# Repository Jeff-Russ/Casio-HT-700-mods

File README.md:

# Casio HT-700 Mods

This is a collection of instruction and schematics (in KiCAD with PCB designs) for modifying the 
Casio HT-700. More info will be available future commits.

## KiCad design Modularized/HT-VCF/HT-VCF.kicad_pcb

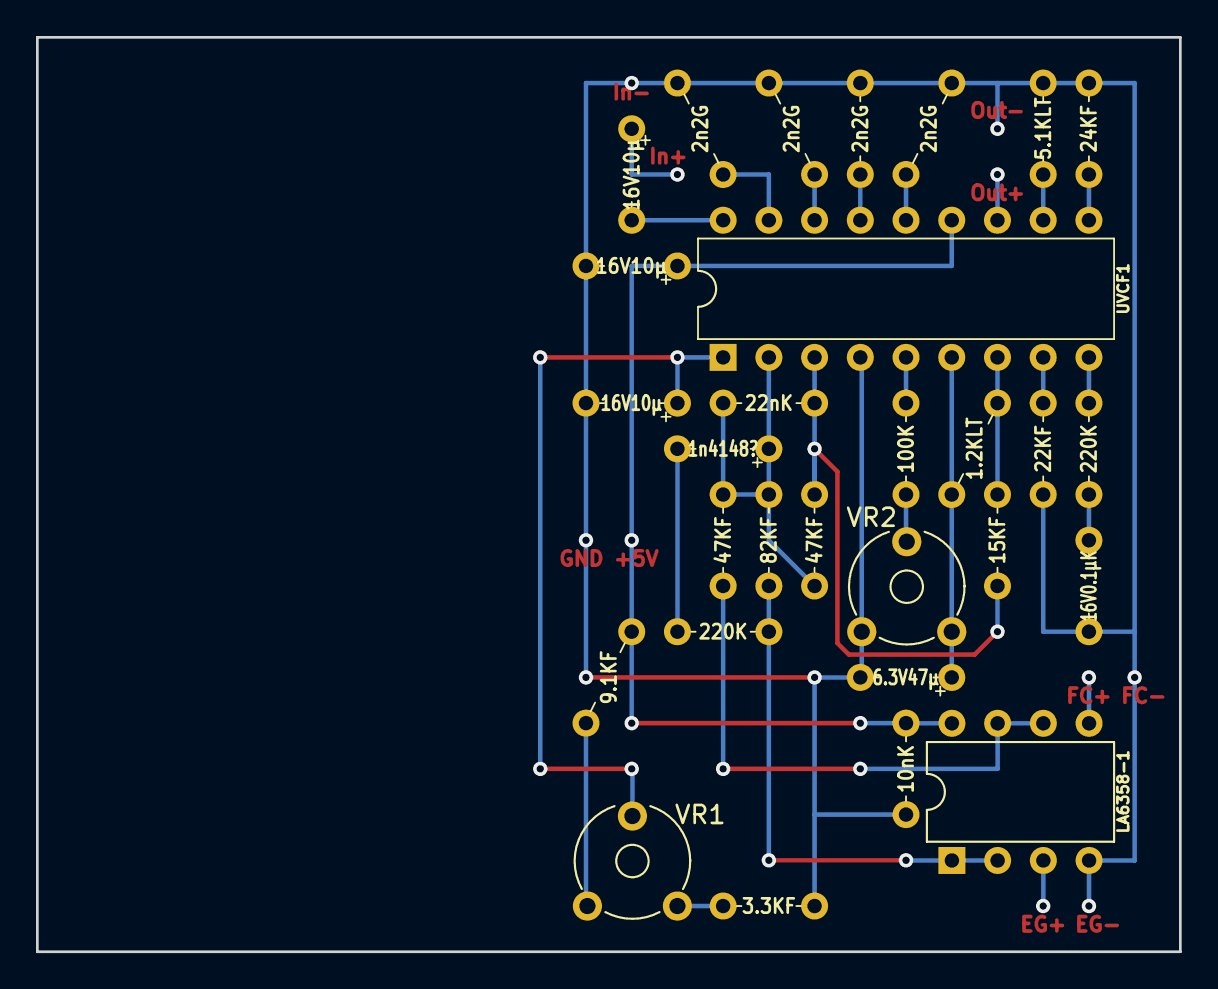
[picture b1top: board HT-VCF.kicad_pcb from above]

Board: 2 copper layers, 63.5 x 50.8 mm, 29 parts (0 on the bottom side), 24 nets.

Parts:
C1, C2, C7: 16V10µ; 200Mil_2TH_Polar_Generic
C3, C4: 2n2G; 200Mil_2TH_Up1_Generic
C5: 2n2G; 200Mil_2TH_Generic
C6: 2n2G; 200Mil_2TH_Dn1_Generic
C8: 22nK; 200Mil_2TH_Generic
C9: 16V0.1µK; 200Mil_2TH_Generic
C10: 6.3V47µ; 200Mil_2TH_Polar_Generic
C11: 10nK; 200Mil_2TH_Generic
D1: 1n4148?; 200Mil_2TH_Polar_Generic
LA6358-1: NJM4558; 300Mil_DIP8
R1: 5.1KLT; 200Mil_2TH_Generic
R2: 24KF; 200Mil_2TH_Generic
R3: 9.1KF; 200Mil_2TH_Dn1_Generic
R4: 3.3KF; 200Mil_2TH_Generic
R5, R12: 47KF; 200Mil_2TH_Generic
R6: 1.2KLT; 200Mil_2TH_Dn1_Generic
R7: 100K; 200Mil_2TH_Generic
R8: 22KF; 200Mil_2TH_Generic
R9, R10: 220K; 200Mil_2TH_Generic
R11: 82KF; 200Mil_2TH_Generic
R13: 15KF; 200Mil_2TH_Generic
UVCF1: NJM2090; 300Mil_DIP18
VR1: B500Ω; Potentiometer_Trimmer_Piher_PT-6v_Horizontal
VR2: B50K; Potentiometer_Trimmer_Piher_PT-6v_Horizontal

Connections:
+5VA: C1.1, C11.2, LA6358-1.8, R3.1, UVCF1.13
/RESO: C9.2, R9.2
/VBB: C7.1, UVCF1.1, VR1.2
GNDA: C1.2, C3.2, C4.2, C5.2, C6.2, C7.2, C9.1, C10.2, C11.1, LA6358-1.4, R1.1, R2.1, R4.2, R8.2, UVCF1.4, VR2.3
unnamed: C2.2, UVCF1.18
unnamed: C3.1, UVCF1.17
unnamed: C4.1, UVCF1.16
unnamed: C5.1, UVCF1.15
unnamed: C6.1, UVCF1.14
unnamed: C8.1, R5.2, R13.2, UVCF1.3
unnamed: C8.2, D1.1, R5.1, R11.2, R12.2, UVCF1.2
unnamed: C10.1, R6.1, UVCF1.6, VR2.1
unnamed: D1.2, R10.2
unnamed: LA6358-1.1, LA6358-1.2, R10.1, R11.1
unnamed: LA6358-1.6, LA6358-1.7, R12.1
unnamed: R1.2, UVCF1.11
unnamed: R2.2, UVCF1.10
unnamed: R3.2, VR1.3
unnamed: R4.1, VR1.1
unnamed: R7.1, UVCF1.5
unnamed: R7.2, VR2.2
unnamed: R8.1, UVCF1.8
unnamed: R9.1, UVCF1.9
unnamed: R6.2, R13.1, UVCF1.7

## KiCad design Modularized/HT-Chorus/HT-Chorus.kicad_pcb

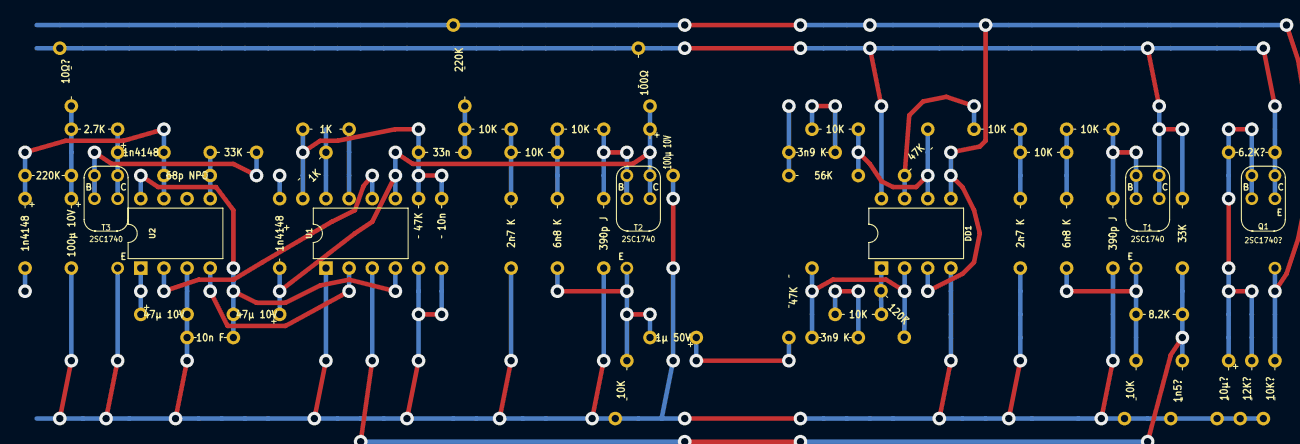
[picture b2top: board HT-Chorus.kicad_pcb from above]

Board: 4 copper layers, 61 parts (0 on the bottom side), 35 nets.

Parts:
C1, C13: 3n9 K; 200Mil_2TH_Generic
C2, C8: 2n7 K; 200Mil_2TH_Generic
C3, C9: 6n8 K; 200Mil_2TH_Generic
C4, C10: 390p J; 200Mil_2TH_Generic
C5: 1n5?; 200Mil_2TH_Generic
C6: 10n; 200Mil_2TH_Generic
C7: 33n; 200Mil_2TH_Generic
C11, C14: 100µ 10V; 200Mil_2TH_Polar_Generic
C12: 1µ 50V; 200Mil_2TH_Polar_Generic
C15, C17: 47µ 10V; 200Mil_2TH_Polar_Generic
C16: 10n F; 200Mil_2TH_Generic
C18: 68p NPO; 200Mil_2TH_Generic
C19: 10µ?; 200Mil_2TH_Polar_Generic
D1, D2, D3: 1n4148; 200Mil_2TH_Polar_Generic
DD1: NJM4558; 300Mil_DIP8
INPUT: REF**; Labled-Circle
LFO: REF**; Labled-Circle
OUTPUT: REF**; Labled-Circle
Q1: 2SC1740?; Universal_BJT_ECB_SM
R1: 56K; 200Mil_2TH_Generic
R2, R4, R5, R6, R7, R12, R13, R14, R16, R19: 10K; 200Mil_2TH_Generic
R3, R10, R17: 47K; 200Mil_2TH_Generic
R8, R23: 33K; 200Mil_2TH_Generic
R9: 8.2K; 200Mil_2TH_Generic
R11, R21: 220K; 200Mil_2TH_Generic
R15: 100Ω; 200Mil_2TH_Generic
R18: 120K; 200Mil_2TH_Generic
R20: 10Ω?; 200Mil_2TH_Generic
R22: 2.7K; 200Mil_2TH_Generic
R24, R25: 1K; 200Mil_2TH_Generic
R26: 6.2K?; 200Mil_2TH_Generic
R27: 12K?; 200Mil_2TH_Generic
R28: 10K?; 200Mil_2TH_Generic
T1, T2, T3: 2SC1740; Universal_BJT_ECB_SM
U1: MN3207; 300Mil_DIP8
U2: MN3102; 300Mil_DIP8
VE: REF**; Labled-Circle

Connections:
+5VA: DD1.8, Q1.2, R8.1, R15.1, R20.2, R26.1, T1.2
/Input: C1.2, R1.1
/Output: DD1.1, R18.2, R19.2
GNDA: C2.1, C4.1, C5.1, C6.2, C8.1, C10.1, C11.2, C14.2, C16.1, C17.2, C19.2, DD1.4, R7.1, R10.1, R16.1, R27.2, R28.2, T3.1, U1.1, U2.3
unnamed: C1.1, R2.1
unnamed: C2.2, R4.2, R5.1
unnamed: C3.1, R7.2, R9.1, T1.1
unnamed: C3.2, R5.2, R6.1
unnamed: C4.2, R6.2, T1.3
unnamed: C5.2, R8.2, R9.2, U1.3
unnamed: C6.1, C7.2, R10.2, R24.1, R25.1
unnamed: C7.1, R11.1, R12.1
unnamed: C8.2, R12.2, R13.1
unnamed: C9.2, R13.2, R14.1
unnamed: C10.2, R14.2, T2.3
unnamed: C11.1, C15.1, D1.2, R15.2, T2.2, U1.5
unnamed: C12.1, R17.1
unnamed: C9.1, C12.2, R16.2, T2.1
unnamed: C13.1, R19.1
unnamed: C13.2, DD1.2, R17.2, R18.1
unnamed: C14.1, R20.1, R21.1, R22.1
unnamed: C15.2, C16.2, U1.4, U2.8
unnamed: C17.1, D1.1, U2.1
unnamed: C18.1, D2.1, D3.2, R21.2, U2.7
unnamed: C18.2, R23.2, U2.5
unnamed: C19.1, Q1.3, R26.2, R27.1
unnamed: D3.1, R22.2, T3.2
unnamed: DD1.6, R1.2, R2.2, R3.1
unnamed: DD1.7, R3.2, R4.1
unnamed: R23.1, T3.3
unnamed: R24.2, U1.7
unnamed: R25.2, U1.8
unnamed: U1.2, U2.4
unnamed: U1.6, U2.2
VE: DD1.3, DD1.5, Q1.1, R11.2, R28.1

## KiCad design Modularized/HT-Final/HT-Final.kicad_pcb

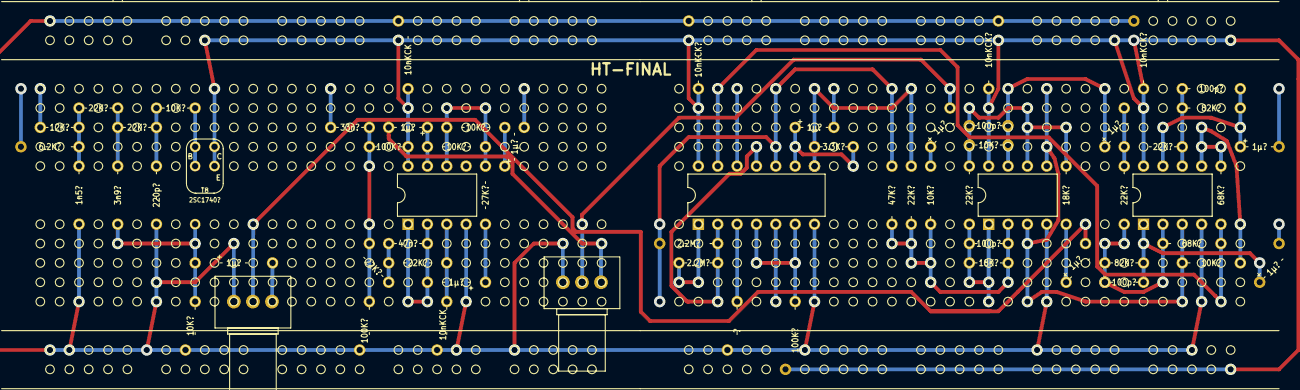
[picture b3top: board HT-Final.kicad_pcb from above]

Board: 2 copper layers, 71 parts (0 on the bottom side), 40 nets.

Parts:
C1, C19: 10nKCK; 200Mil_2TH_Generic
C2, C26, C32: 10nKCK?; 200Mil_2TH_Generic
C6: 1n5?; 200Mil_2TH_Generic
C8: 3n9?; 200Mil_2TH_Generic
C11: 220p?; 200Mil_2TH_Generic
C13: 33n?; 200Mil_2TH_Generic
C14: ?; 200Mil_2TH_Generic
C15, C16, C17, C22, C23, C24, C25, C29, C33, C34: 1µ?; 200Mil_2TH_Polar_Generic
C18: 47n?; 200Mil_2TH_Generic
C20, C27, C30, C31: 100p?; 200Mil_2TH_Generic
CH0, CH1: REF**; Labled-Circle
DD2, DD3: NJM4558; 300Mil_DIP8
LVCF(M): REF**; Labled-Circle
NJM4558-1: NJM4558; 300Mil_DIP8
PERC9: REF**; Labled-Circle
R3: 6.2K?; 200Mil_2TH_Generic
R4: 12K?; 200Mil_2TH_Generic
R11, R13, R23, R28, R30, R35, R43, R44: 22K?; 200Mil_2TH_Generic
R17, R20, R24, R29, R31, R38, R46: 10K?; 200Mil_2TH_Generic
R21, R22, R27: 100K?; 200Mil_2TH_Generic
R25: 27K?; 200Mil_2TH_Generic
R26: 3.3K?; 200Mil_2TH_Generic
R32: 47K?; 200Mil_2TH_Generic
R33, R36: 18K?; 200Mil_2TH_Generic
R34, R37: 2.2M?; 200Mil_2TH_Generic
R42, R45: 68K?; 200Mil_2TH_Generic
R47, R48: 82K?; 200Mil_2TH_Generic
RV1, RV2: B50K?; Pot_TH_Mini_pcbEdge
T8: 2SC1740?; Universal_BJT_ECB_SM
TC4066-2: TC4066-2; 300Mil_DIP14
UVCF(M): REF**; Labled-Circle
VAL**: REF**; breadboard-endless
VAL**#2: REF**; breadboard-endless
VE: REF**; Labled-Circle

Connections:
+5VA: C2.2, C19.2, C26.2, C32.2, DD2.8, DD3.8, NJM4558-1.8, R21.1, R27.1, T8.2, TC4066-2.14
/ACC: C22.1, NJM4558-1.7, R31.1
/ACCOMP: C24.2, RV1.2
/ADRY: C24.1, R29.2
/ChFB: R32.2, R34.2, TC4066-2.10
/ChWet: R42.1, R45.1, TC4066-2.13
/FromCh: R37.2, TC4066-2.1
/MDRY: R26.2, R28.2, TC4066-2.8
/MONO: C29.2, R43.1, R44.1
/RHY: C8.1, C23.1, R20.2, T8.1
/RHYTHM: C25.2, RV2.2
/ToCh: C20.1, DD2.1, R33.2, R35.1
GNDA: C1.2, C2.1, C6.1, C11.1, C14.2, C19.1, C26.1, C32.1, DD2.4, DD3.4, NJM4558-1.4, R20.1, R22.2, RV1.1, RV2.1, TC4066-2.7
unnamed: C1.1, NJM4558-1.3, R30.2
unnamed: C6.2, R3.1, R4.1, R11.1
unnamed: C8.2, R11.2, R13.1
unnamed: C11.2, R13.2, R17.1
unnamed: C13.1, R21.2, R22.1, R23.1
unnamed: C14.1, TC4066-2.3
unnamed: C15.1, R26.1, TC4066-2.9
unnamed: C16.1, R24.2
unnamed: C17.1, R25.2
unnamed: C17.2, C18.1, NJM4558-1.1, NJM4558-1.2
unnamed: C18.2, R23.2, R30.1
unnamed: C20.2, DD2.2, R28.1, R29.1, R32.1, R33.1
unnamed: C22.2, RV1.3
unnamed: C23.2, RV2.3
unnamed: C25.1, R36.2
unnamed: C27.1, C29.1, DD2.7, R38.2
unnamed: C27.2, DD2.6, R35.2, R36.1, R38.1
unnamed: C30.1, C33.1, DD3.1, R47.2
unnamed: C30.2, DD3.2, R42.2, R43.2, R47.1
unnamed: C31.1, C34.1, DD3.7, R48.2
unnamed: C31.2, DD3.6, R44.2, R48.1
unnamed: DD3.5, R45.2, R46.1
unnamed: NJM4558-1.6, R24.1, R25.1, R31.2
unnamed: R17.2, T8.3
unnamed: R27.2, TC4066-2.4, TC4066-2.6
unnamed: R34.1, R37.1, TC4066-2.2, TC4066-2.11
VE: DD2.3, DD2.5, DD3.3, R46.2

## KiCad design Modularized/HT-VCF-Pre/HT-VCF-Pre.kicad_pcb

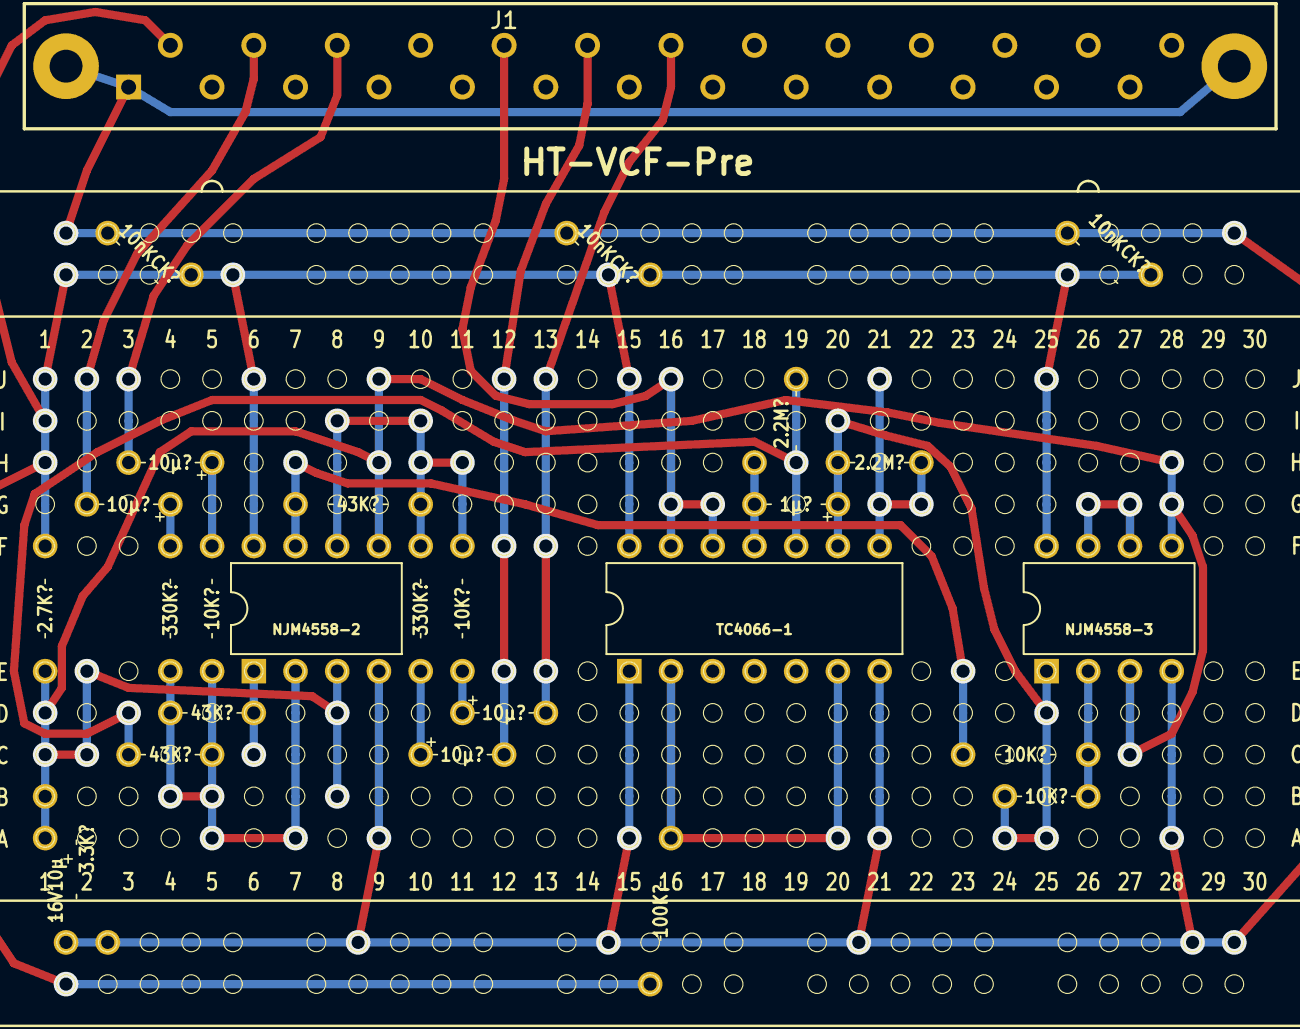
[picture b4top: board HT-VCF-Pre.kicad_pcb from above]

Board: 2 copper layers, 31 parts (0 on the bottom side), 23 nets.

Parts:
C1: 16V10µ; 200Mil_2TH_Polar_Generic
C2, C3, C4, C5: 10µ?; 200Mil_2TH_Polar_Generic
C7: 1µ?; 200Mil_2TH_Polar_Generic
C9, C10, C12: 10nKCK?; 200Mil_2TH_Generic
J1: DB25_Female; DB25-Shielded-zigzag
LOSC: REF**; Labled-Circle
NJM4558-2, NJM4558-3: NJM4558; 300Mil_DIP8
R1: 2.7K?; 200Mil_2TH_Generic
R2: 3.3K?; 200Mil_2TH_Generic
R5, R19: 2.2M?; 200Mil_2TH_Generic
R6, R8: 330K?; 200Mil_2TH_Generic
R7, R9, R15, R18: 10K?; 200Mil_2TH_Generic
R10, R12, R14: 43K?; 200Mil_2TH_Generic
R16: 100K?; 200Mil_2TH_Generic
TC4066-1: TC4066-1; 300Mil_DIP14
UOSC: REF**; Labled-Circle
VAL**: REF**; breadboard-30-4Rail
VBC: REF**; Labled-Circle

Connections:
+5VA: C9.2, C10.2, C12.2, J1.14, NJM4558-2.8, NJM4558-3.8, R1.1, R16.1, TC4066-1.14
/LBIT: C2.2, J1.19
/LOSC: R19.2, TC4066-1.8
/LTONE: C3.2, J1.20
/N: J1.18, TC4066-1.12, TC4066-1.13
/UBIT: C4.2, J1.15
/UOSC: NJM4558-2.1, R14.2
/UTONE: C5.2, J1.16
GNDA: C1.2, C9.1, C10.1, C12.1, J1.0, J1.1, NJM4558-2.4, NJM4558-3.4, R2.2, TC4066-1.1, TC4066-1.7
unnamed: C2.1, R6.1
unnamed: C3.1, R7.1
unnamed: C4.1, R8.1
unnamed: C5.1, R9.1
unnamed: C7.1, NJM4558-3.1, R18.2, R19.1, TC4066-1.9
unnamed: C7.2, R5.2, TC4066-1.11
unnamed: NJM4558-2.2, R8.2, R9.2, R10.2, R14.1
unnamed: NJM4558-2.6, R6.2, R7.2, R12.1
unnamed: NJM4558-2.7, R12.2, R15.1
unnamed: NJM4558-3.2, R15.2, R18.1
unnamed: NJM4558-3.6, NJM4558-3.7
unnamed: R5.1, R10.1, TC4066-1.10
unnamed: R16.2, TC4066-1.2, TC4066-1.6
VBC: C1.1, NJM4558-2.3, NJM4558-2.5, NJM4558-3.3, NJM4558-3.5, R1.2, R2.1

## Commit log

2017-09-08 update LFO design
2018-04-12 updating with modularized version
2018-04-19 save point
